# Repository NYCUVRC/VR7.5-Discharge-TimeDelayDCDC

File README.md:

# VR7.5-Discharge-TimeDelayDCDC
A KiCad project for Discharge&amp;TimeDelayDCDC PCB

## Front

## Back

## Features
- [x] Schematic
  - [x] At least 5s Time Delay on DCDC output
  - [x] Flyback Diode beside coils
  - [x] ALL Spice Model
  - [x] Simulation Success
  - [x] Electrical Rules Check(ERC)
- [x] PCB
  - [x] Mounting Holes
  - [x] Test Points
  - [x] Wide Traces on HV
  - [x] Mark Distance between HV and LV
  - [x] Ground Plane
  - [x] Version Number
  - [x] Design Rules Check(DRC)
- [ ] Manufacturing
  - [x] Gerber Files
  - [x] Drill Files
  - [x] BOM
  - [ ] Pick and Place File
- [x] Assembly
  - [x] Soldering
  - [x] Testing
  - [x] Debugging

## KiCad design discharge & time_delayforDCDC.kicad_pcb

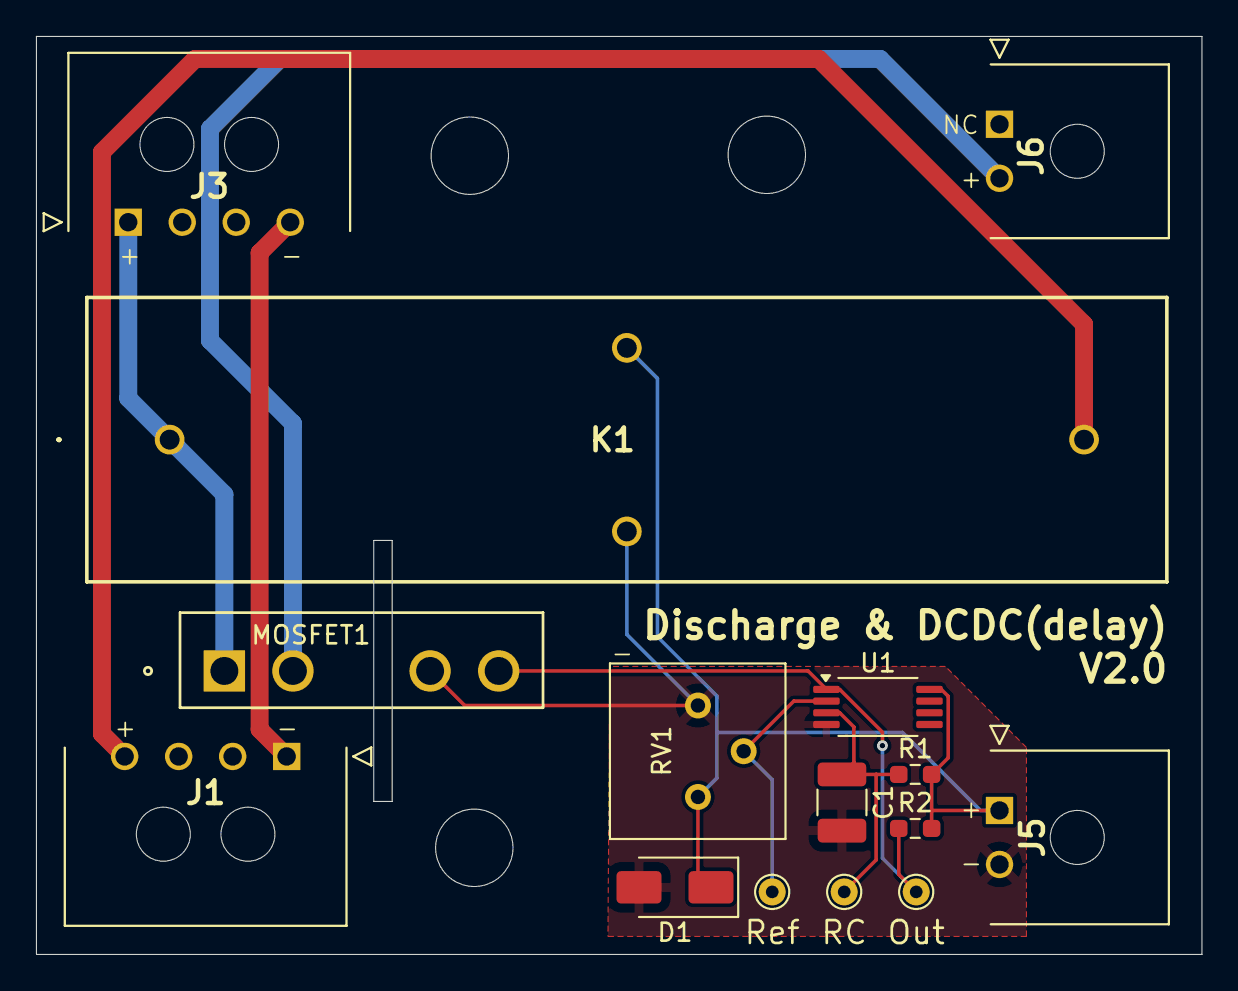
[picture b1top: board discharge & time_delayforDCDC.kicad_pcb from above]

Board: 2 copper layers, 64.8 x 51.0 mm, 18 parts (0 on the bottom side), 9 nets.

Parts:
C1: 100u; C_1210_3225Metric_Pad1.33x2.70mm_HandSolder
D1: US1J; D_SMA
H1, H2, H3: MountingHole; MountingHole_4.3mm_M4
J1, J3: 43650-0400; 43650-04_00,01,02_
J5, J6: 43650-0200; 43650-02_00,01,02_
K1: DBT71205U
MOSFET1: CPC1968J; ISOPLUS-264_19P914X5P029_IXY
R1: 50k; R_0603_1608Metric_Pad0.98x0.95mm_HandSolder
R2: 1k; R_0603_1608Metric_Pad0.98x0.95mm_HandSolder
RV1: R_Potentiometer; Potentiometer_Bourns_3386P_Vertical
TP1, TP2, TP3: TestPoint; TestPoint_THTPad_D1.5mm_Drill0.7mm
U1: LM393; TSSOP-8_4.4x3mm_P0.65mm

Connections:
/Delay: C1.1, R1.1, TP1.1, U1.3 (+)
/Enable: MOSFET1.4, R2.1, TP2.1, U1.1
/Ref: RV1.2, TP3.1, U1.2 (-)
DCDC: J6.2, MOSFET1.2
Discharge: J1.4, K1.2 (out-)
GND: C1.2, D1.2 (A), J5.2, K1.3 (-), MOSFET1.3, RV1.3, U1.4 (V-)
SDC: D1.1 (K), J5.1, K1.4 (+), R1.2, R2.2, RV1.1, U1.8 (V+)
TS+: J3.1, K1.1 (out+), MOSFET1.1
TS-: J1.1, J3.4

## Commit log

2025-04-30 upload pcb images
2025-04-30 update README with features and project details
2025-04-30 feat: add manufacturing and assembly sections to README
2025-04-30 Update schematic and PCB
    - Modified properties of test points to exclude from simulation and removed from BOM
    - Fix wrong rating of the capacitor
    - Updated footprint
    - Updated image file
2025-04-30 Update README.md
    - add back pcb image
2025-04-30 remove Gerber - Only download Gerbers on Release page
